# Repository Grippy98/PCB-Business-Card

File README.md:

# PCB-Business-Card
---

Business Cards are always something that I’ve found to be sort of a nuisance. On one hand, they’re something that very few people ever have on hand, and on the other, when you do get one, you’re very likely to misplace or throw it away. That being said, they are a good way of sharing your contact details, and while I have made my own nicely designed ones on paper, I couldn’t help but think that I could make something better. My goal here was to make something that not only could I be proud to give out to possible recruiters or people I’d want to contact in the future, but I wanted to make something they’d actually WANT to keep with them or in their wallet.

Therefore I set out to design what you see before you, my very own extremely functional PCB business card. I credit it for a good number of job interviews I've gotten this past summer. It's a constant work in progress, but I'm very pleased with how it's turned out. 

###### A huge shoutout to Loann Boudin for his NFC design and for documenting it on Instructables: https://www.instructables.com/id/PCB-Business-Card-With-NFC/

### As far as the card’s functionality goes: 

1. 1S Lithium Battery Charger 
2. NFC Enabled - Have it setup to link to my Website/Resume (also demonstrates power harvesting to LED)
3. Simple logic probe that will tell you if a signal is high/low, oscillating or floating (the last two perhaps are especially useful)
4. Basic flash light (because why not) 
5. Metric/imperial Ruler
6. AWG Gauge 
7. References for trace widths in Mils 
8. Reference for PCB Font Sizes 
9. Reference for some standard component footprints

---

### Ordering Your Own

The Boards you see were made by JLC PCB with an ENIG finnish, regular LEAD free also works. I do very much recommend you don't hand out leaded PCBs for people to handle and keep in their wallets, but that's just my two cents.

I have experimented with 0.6mm Thick Boards and above, but I recommend 0.8mm as it's thin enough while also being a bit more rigid. 

### BOM:
(TODO - fill out when I have some more time, consult schematic otherwise)
1x BRCL4054BME Power Management IC

### Notes on Soldering:

It's all rather easy to solder by hand, save for the QFN8 Package of the NFC IC, which is tough to get right, especially with Lead-free solder paste. I was able to make over 30 of these boards without defect and minor fixes by using solder masks and plenty of flux, but this is very much not beginner friendly.

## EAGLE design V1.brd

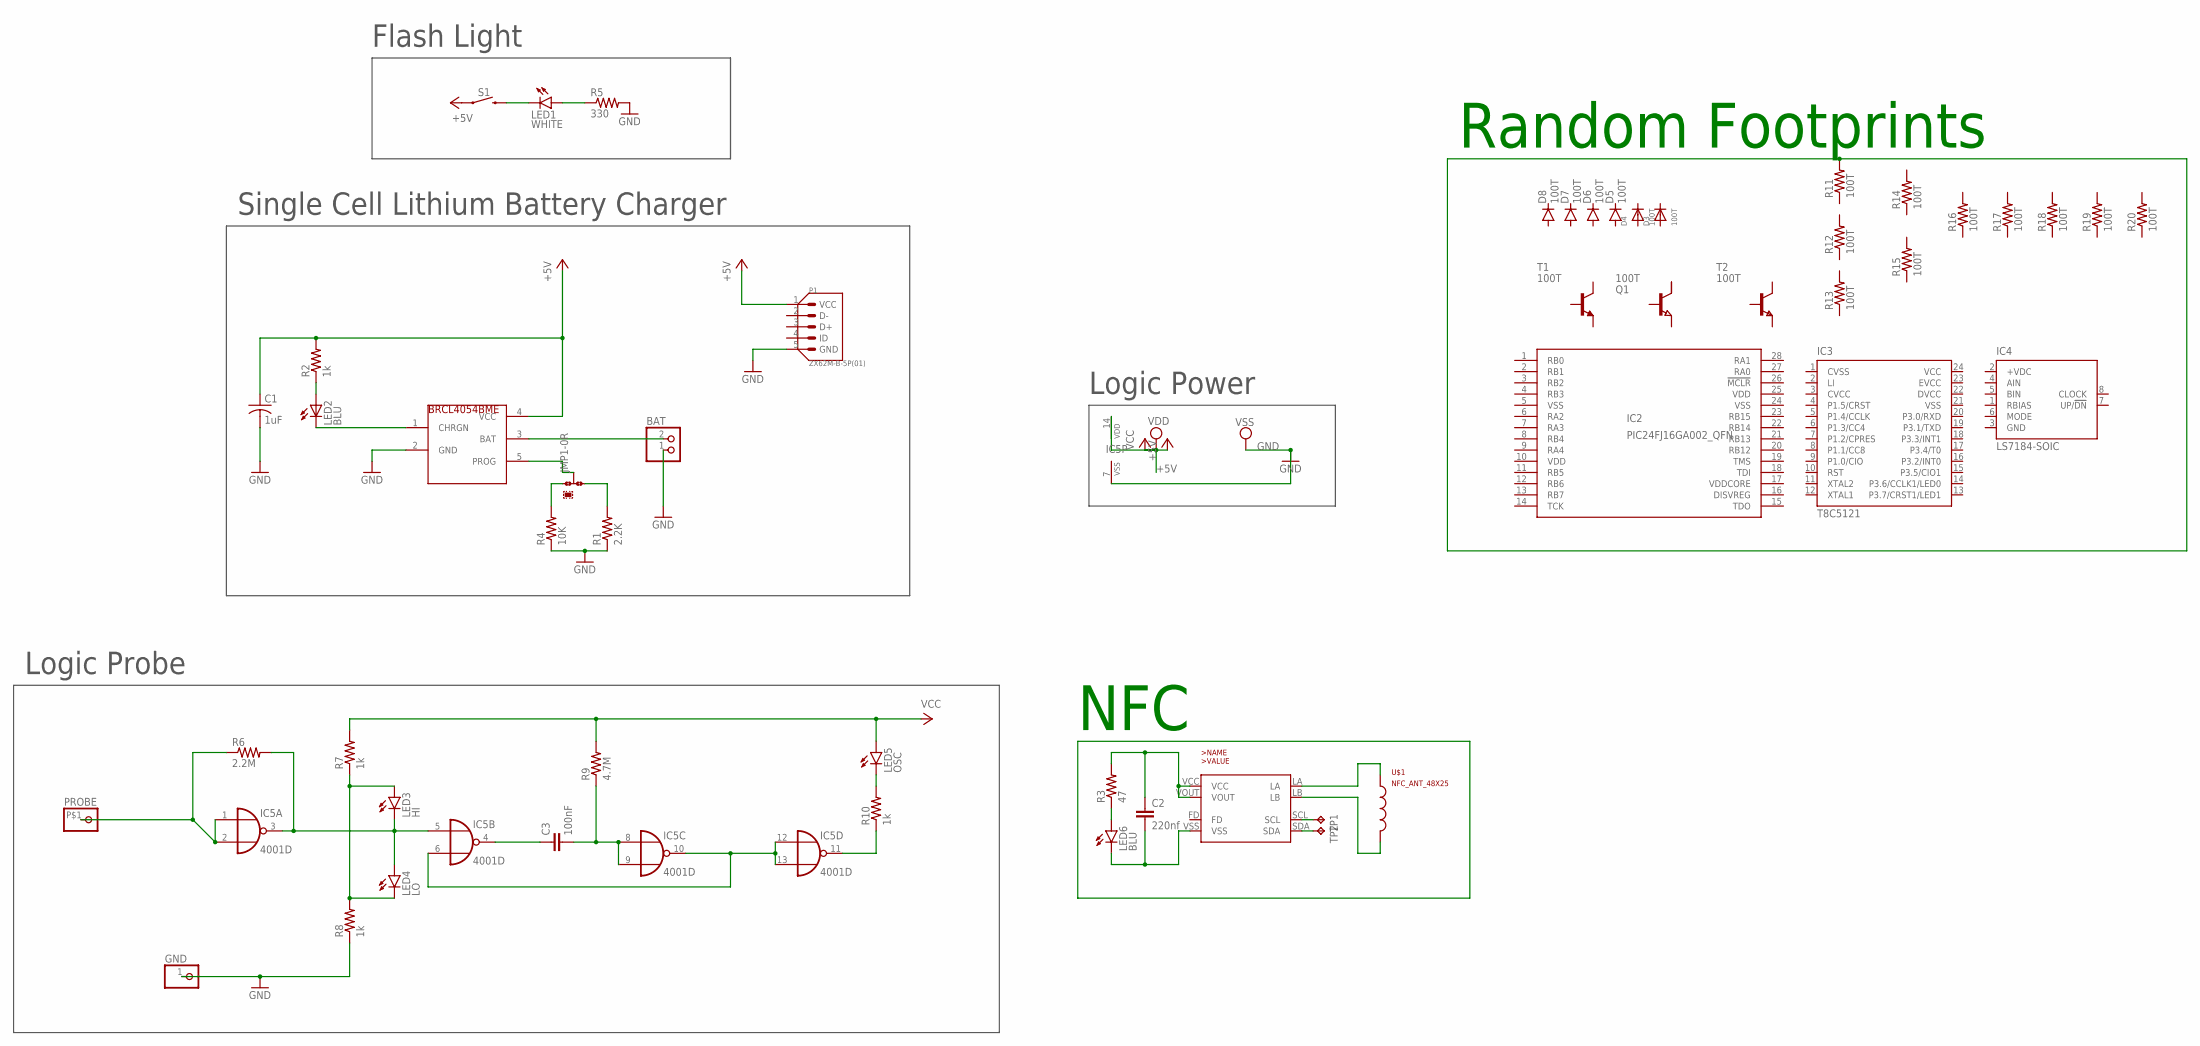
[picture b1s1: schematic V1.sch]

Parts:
BAT: JST_2PIN-SMT; JST-PH-2-SMT
C1: 1uF; C0402
C2: 220nf; C0402
C3: 100nF; C0402
D3: 100T; SMADIODE
D4: 100T; SOD-123
D5: 100T; SOD80C
D6: 100T; SOD323-R
D7: 100T; MICROMELF-R
D8: 100T; SC79_INFINEON
GND: PINHD-1X1; 1X01
IC2: PIC24FJ16GA002_QFN; QFN28-ML_6X6MM
IC3: T8C5121; SSOP24
IC4: LS7184-SOIC; SOIC08
IC5: 4001D; SO14
JMP1: 0R-JUMPA; A0R-JMP
LED1: WHITE; LED3MM
LED2: BLU; CHIP-LED0603
LED3: HI; SML0603
LED4: LO; SML0603
LED5: OSC; SML0603
LED6: BLU; SML0603
NT3H1101: NT3H1101; XQFN8
P1: ZX62M-B-5P(01); HRS_ZX62M-B-5P(01)
PROBE: PINHD-1X1-BIGPOGO; 1X1-BIGPOGO
Q1: 100T; SOT89
R1: 2.2K; R0402
R2, R7, R8, R10: 1k; R0402
R3: 47; R0402
R4: 10K; R0402
R5: 330; R0402
R6: 2.2M; R0402
R9: 4.7M; R0402
R11, R12, R13: 100T; R0201
R14, R15: 100T; R0402
R16: 100T; R0603
R17: 100T; R0805
R18: 100T; R1206
R19: 100T; R1210
R20: 100T; R2010
S1: MOMENTARY-SWITCH-SPST-SMD-5.2-REDUNDANT; TACTILE_SWITCH_SMD_5.2MM
T1: 100T; SOT23-EBC
T2: 100T; SOT223
TP1, TP2: TPTP06R; TP06R
U$1: NFC_ANT_48X25
U$3: HX4054A; SOT23-5L

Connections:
+5V: C1.1, IC2.10 (VDD), IC2.25 (VDD), IC3.24 (VCC), IC5.14 (VDD), P1.1 (VCC), R2.2, S1.1, S1.2 (1), U$3.4 (VCC)
CVCC: IC3.3 (CVCC)
CVSS: IC3.1 (CVSS)
DVCC: IC3.22 (DVCC)
GND: BAT.1 (2), C1.2, GND.1, IC2.5 (VSS), IC2.24 (VSS), IC3.21 (VSS), IC4.3 (GND), IC5.7 (VSS), P1.5 (GND), R1.1, R4.1, R5.2, R8.1, U$3.2 (GND)
LI: IC3.2 (LI)
unnamed: JMP1.3, R1.2
unnamed: LED2.A, R2.1
unnamed: LED2.C, U$3.1 (CHRGN)
unnamed: BAT.2 (1), U$3.3 (BAT)
unnamed: JMP1.2, U$3.5 (PROG)
unnamed: LED1.A, R5.1
unnamed: IC5.6 (I1), IC5.10 (O), IC5.12 (I0), IC5.13 (I1)
unnamed: IC5.1 (I0), IC5.2 (I1), PROBE.P$1, R6.1
unnamed: LED3.A, LED4.C, R7.1, R8.2
unnamed: C3.2, IC5.8 (I0), R9.1
unnamed: NT3H1101.LA, U$1.A
unnamed: NT3H1101.LB, U$1.B, U$1.P$3 (B)
unnamed: C2.1, NT3H1101.VCC, NT3H1101.VOUT, R3.2
unnamed: LED6.A, R3.1
unnamed: C2.2, LED6.C, NT3H1101.VSS
unnamed: IC5.3 (O), IC5.5 (I0), LED3.C, LED4.A, R6.2
unnamed: NT3H1101.SDA, TP2.TP
unnamed: NT3H1101.SCL, TP1.TP
unnamed: C3.1, IC5.4 (O)
unnamed: IC5.11 (O), R10.1
unnamed: LED5.C, R10.2
unnamed: JMP1.1, R4.2
unnamed: LED1.K (C), S1.3 (2), S1.4 (2)
VCC: LED5.A, R7.2, R9.2
VDDCORE: IC2.17 (VDDCORE)

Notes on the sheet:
Logic Probe
Single Cell Lithium Battery Charger
Flash Light
Logic Power
Random Footprints
NFC

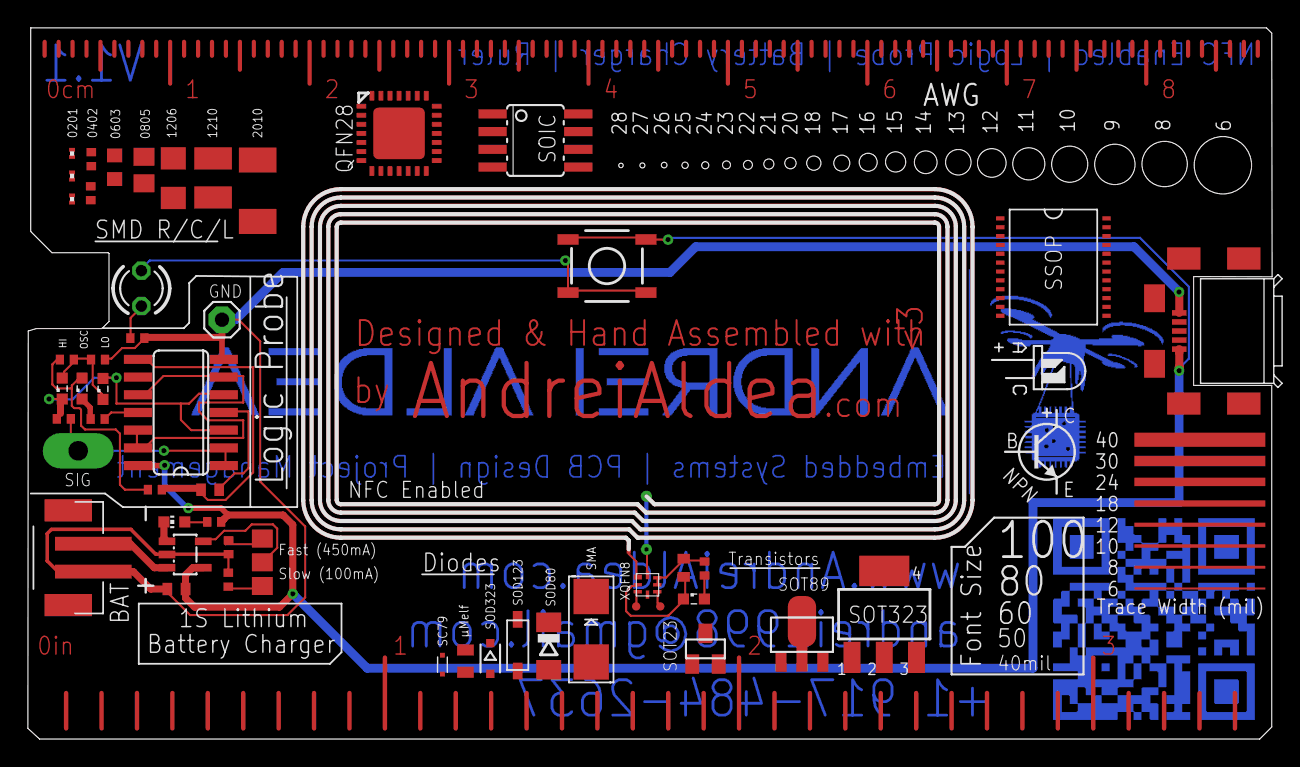
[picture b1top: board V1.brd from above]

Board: 2 copper layers, 89.2 x 51.0 mm, 57 parts (1 on the bottom side), 26 nets.

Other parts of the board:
E$54: NPN-SYMB
E$74: LED-GUIDE
U$2: IMPERIAL
U$4: METRIC

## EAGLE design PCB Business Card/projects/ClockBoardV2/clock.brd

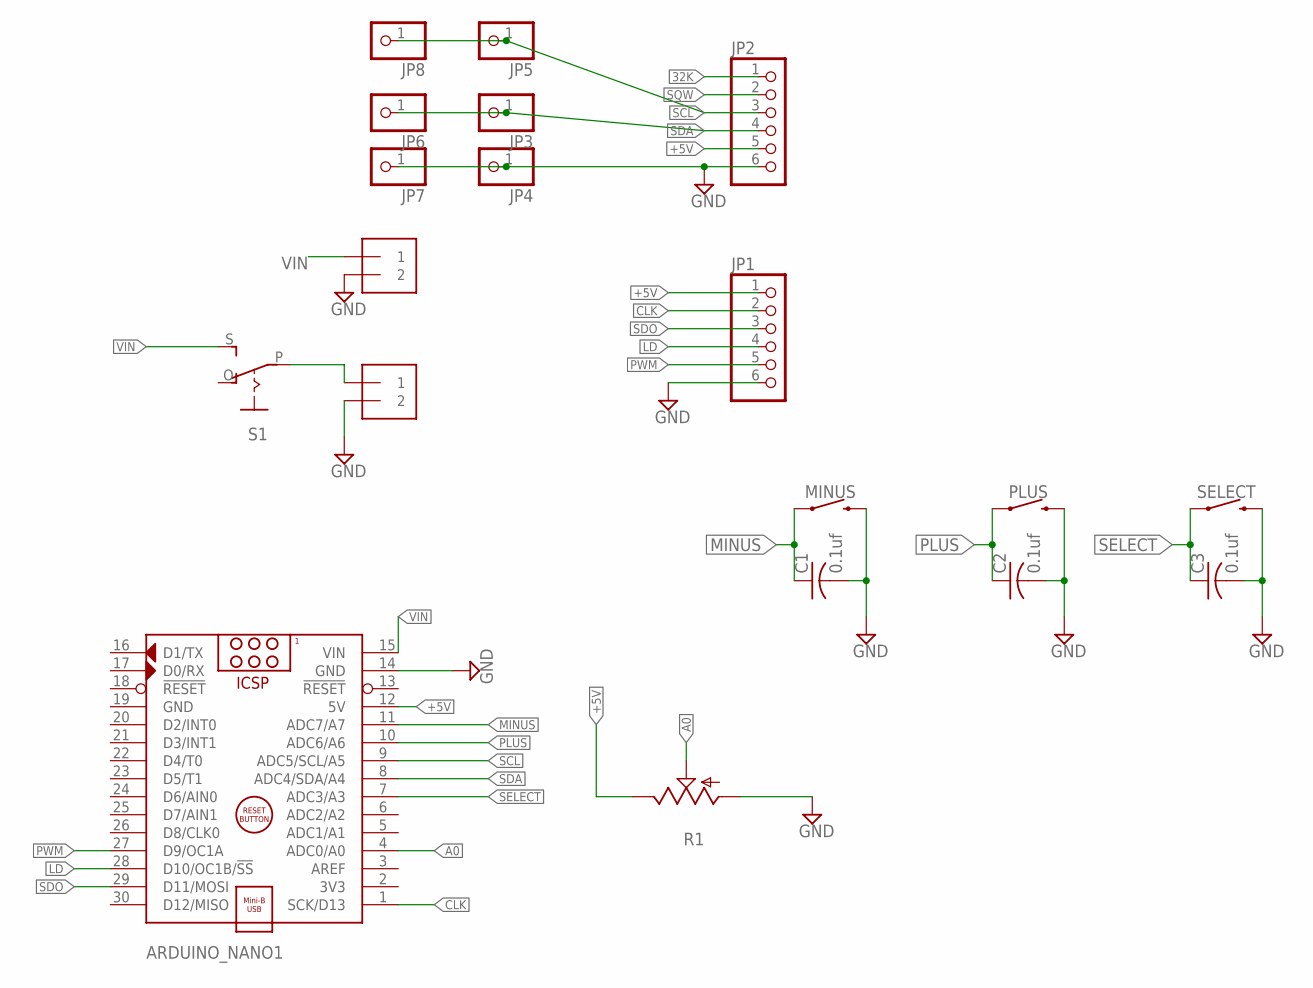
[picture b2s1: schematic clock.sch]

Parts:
ARDUINO_NANO1: ARDUINO_NANO
C1, C2, C3: 0.1uf; C025-025X050
J1, J2: 1X2-3.5MM
JP1, JP2: PINHD-1X6; 1X06
JP3, JP4, JP5, JP6, JP7, JP8: PINHD-1X1; 1X01
MINUS: MOMENTARY-SWITCH-SPST-PTH-6.0MM; TACTILE_SWITCH_PTH_6.0MM
PLUS: MOMENTARY-SWITCH-SPST-PTH-6.0MM; TACTILE_SWITCH_PTH_6.0MM
R1: TRIM_US-RS3; RS3
S1: EG1218S; EG1218
SELECT: MOMENTARY-SWITCH-SPST-PTH-6.0MM; TACTILE_SWITCH_PTH_6.0MM

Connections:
32K: JP2.1
+5V: ARDUINO_NANO1.12 (5V), JP1.1, JP2.5, R1.E
A0: ARDUINO_NANO1.4 (ADC0/A0), R1.S
CLK: ARDUINO_NANO1.1 (SCK/D13), JP1.2
GND: ARDUINO_NANO1.14 (GND), ARDUINO_NANO1.19 (GND), C1.2, C2.2, C3.2, J1.2, J2.2, JP1.6, JP2.6, JP4.1, JP7.1, MINUS.3 (2), PLUS.3 (2), R1.A, SELECT.3 (2)
LD: ARDUINO_NANO1.28 (D10/OC1B/!SS), JP1.4
MINUS: ARDUINO_NANO1.11 (ADC7/A7), C1.1, MINUS.1
unnamed: J1.1, S1.P
PLUS: ARDUINO_NANO1.10 (ADC6/A6), C2.1, PLUS.1
PWM: ARDUINO_NANO1.27 (D9/OC1A), JP1.5
SCL: ARDUINO_NANO1.9 (ADC5/SCL/A5), JP2.3, JP5.1, JP8.1
SDA: ARDUINO_NANO1.8 (ADC4/SDA/A4), JP2.4, JP3.1, JP6.1
SDO: ARDUINO_NANO1.29 (D11/MOSI), JP1.3
SELECT: ARDUINO_NANO1.7 (ADC3/A3), C3.1, SELECT.1
SQW: JP2.2
VIN: ARDUINO_NANO1.15 (VIN), J2.1, S1.S

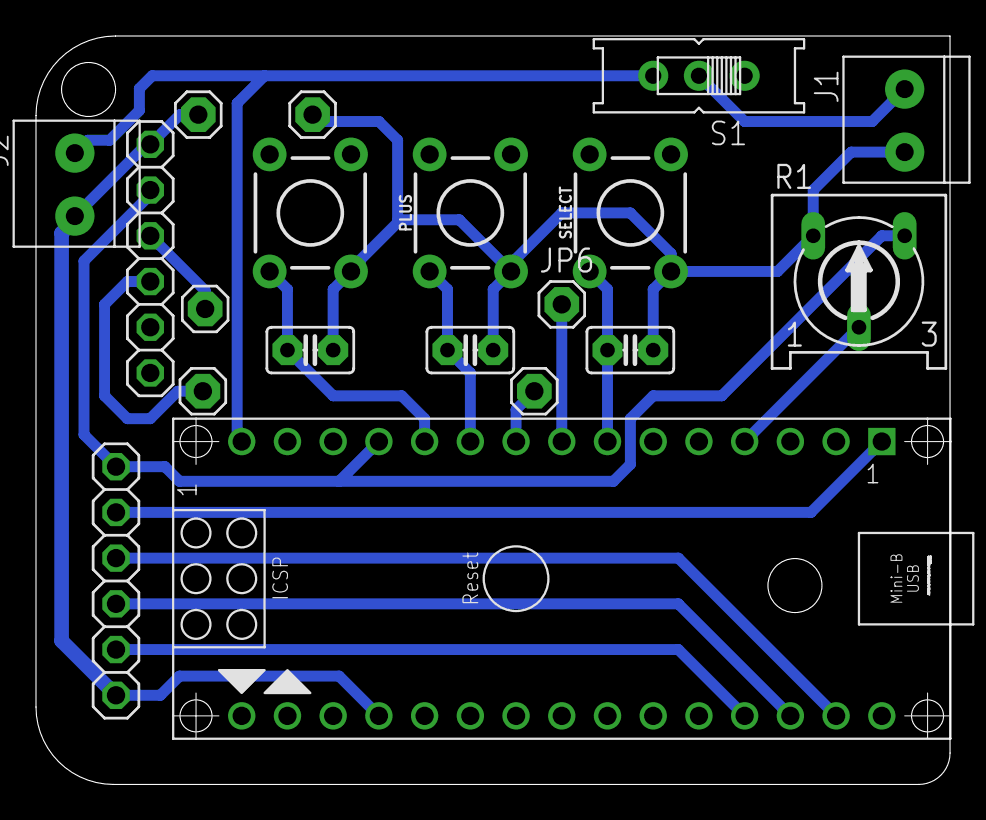
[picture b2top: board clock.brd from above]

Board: 2 copper layers, 50.8 x 41.6 mm, 19 parts (0 on the bottom side), 14 nets.

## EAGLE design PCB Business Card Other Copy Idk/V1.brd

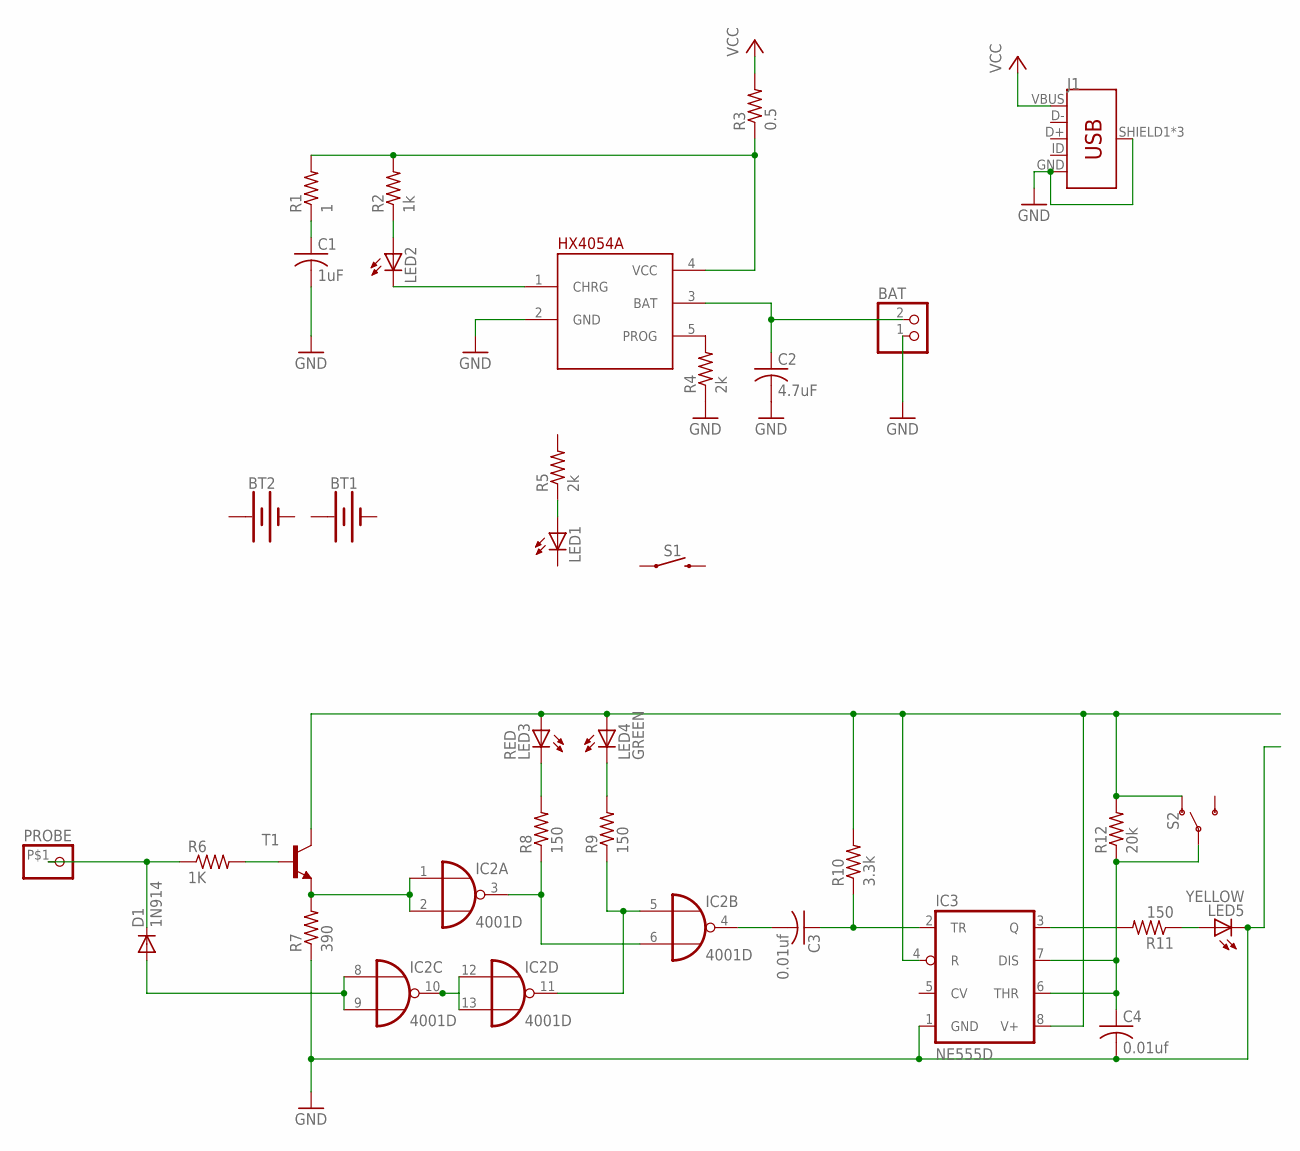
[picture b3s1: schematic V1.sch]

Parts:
BAT: JST_2PIN-SMT; JST-PH-2-SMT
BT1, BT2: BATTERY-12MM_SMD; BATTCON_12MM
C1: 1uF; C0402
C2: 4.7uF; C0402
C3, C4: 0.01uf; C0402
D1: 1N914; SOD323-W
IC2: 4001D; SO14
IC3: NE555D; SO08
J1: USB_MICRO-BREDUCED_PASTE; USB-B-MICRO-SMD_RED_PASTE
LED1: LED3MM
LED2: LEDCHIP-LED0603; CHIP-LED0603
LED3: RED; CHIP-LED0603
LED4: GREEN; CHIP-LED0603
LED5: YELLOW; CHIP-LED0603
PROBE: PINHD-1X1-BIGPOGO; 1X1-BIGPOGO
R1: 1; R0201
R2: 1k; R0201
R3: 0.5; R0402
R4: 2k; R0201
R5: 2k; R0603
R6: 1K; R0402
R7: 390; R0402
R8, R9, R11: 150; R0402
R10: 3.3k; R0402
R12: 20k; R0402
S1: MOMENTARY-SWITCH-SPST-SMD-5.2-REDUNDANT; TACTILE_SWITCH_SMD_5.2MM
S2: SWITCH-SPDT-PTH-11.6X4.0MM; SWITCH_SPDT_PTH_11.6X4.0MM
T1: MMBT2222ALT1-NPN-SOT23-BEC; SOT23-BEC
U$3: HX4054A; SOT23-5L

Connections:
+: BT1.PWR@1 (+), BT2.PWR@1 (+)
-: BT1.GND (-), BT2.GND (-)
GND: BAT.1 (2), C1.2, C2.2, C4.2, IC3.1 (GND), J1.GND, J1.SHIELD1 (SHIELD), J1.SHIELD2 (SHIELD), J1.SHIELD3 (SHIELD), LED5.C, R4.1, R7.1, U$3.2 (GND)
unnamed: C1.1, R1.1
unnamed: R1.2, R2.2, R3.1, U$3.4 (VCC)
unnamed: LED2.A, R2.1
unnamed: LED2.C, U$3.1 (CHRG)
unnamed: BAT.2 (1), C2.1, U$3.3 (BAT)
unnamed: R4.2, U$3.5 (PROG)
unnamed: LED1.A, R5.1
unnamed: R6.2, T1.B
unnamed: D1.C, PROBE.P$1, R6.1
unnamed: D1.A, IC2.8 (I0), IC2.9 (I1)
unnamed: IC2.10 (O), IC2.12 (I0), IC2.13 (I1)
unnamed: IC2.1 (I0), IC2.2 (I1), R7.2, T1.E
unnamed: LED3.C, R8.2
unnamed: LED4.C, R9.2
unnamed: IC2.3 (O), IC2.6 (I1), R8.1
unnamed: IC2.5 (I0), IC2.11 (O), R9.1
unnamed: LED5.A, R11.1
unnamed: IC3.3 (Q), R11.2
unnamed: C3.2, IC2.4 (O)
unnamed: C3.1, IC3.2 (TR), R10.1
unnamed: C4.1, IC3.6 (THR), IC3.7 (DIS), R12.1, S2.2
unnamed: IC3.4 (R), IC3.8 (V+), LED3.A, LED4.A, R10.2, R12.2, S2.1 (O), T1.C
VCC: J1.VBUS, R3.2
VDD: IC2.14 (VDD)
VSS: IC2.7 (VSS)

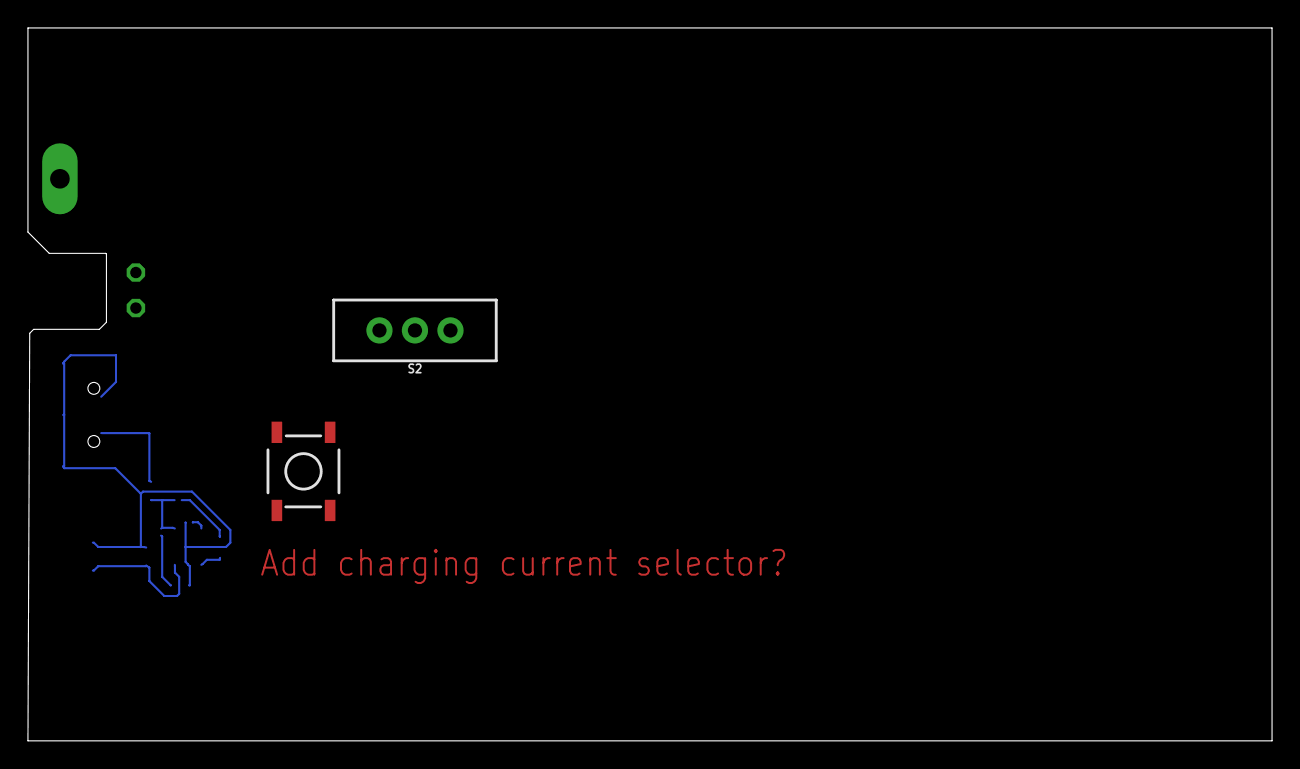
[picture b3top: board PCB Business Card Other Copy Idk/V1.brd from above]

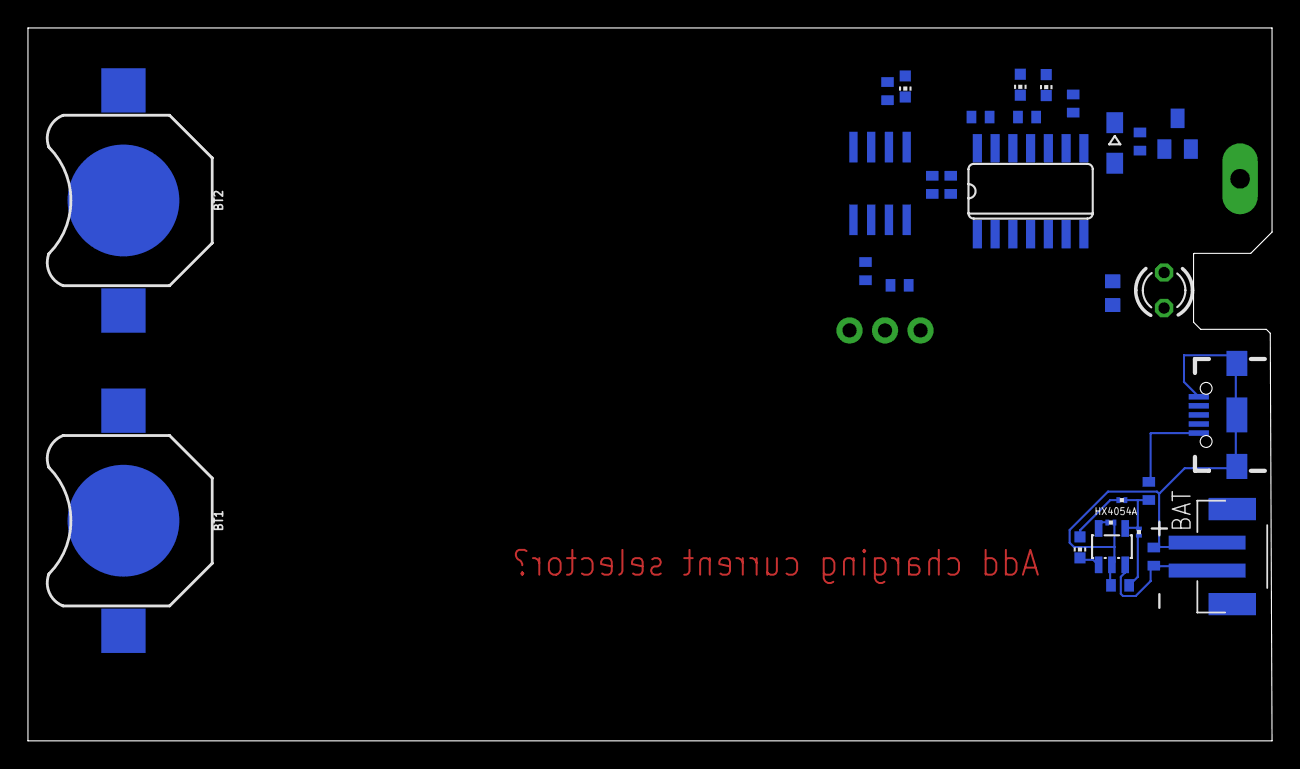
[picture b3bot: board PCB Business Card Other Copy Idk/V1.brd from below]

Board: 2 copper layers, 89.0 x 51.0 mm, 35 parts (30 on the bottom side), 26 nets.

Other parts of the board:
U$1: METRIC
U$2: IMPERIAL

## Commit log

2019-07-24 O no I'm getting ideas
2019-07-25 Really Proud of How its TUrning out... Almost done
2019-07-26 V1 Completed
2019-07-29 Version that went into production
2019-08-02 4001 and 74 Series logic Pinout is Different... DOH
2019-08-26 I made changes aparently
2019-08-29 V1.1 Ordered From JLC
2020-04-01 Cleanning Up
2020-04-01 Fixed Images
2020-04-01 Cleanup

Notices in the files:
parts and their libraries:
SparkFun-Switches: Licensing: Creative Commons ShareAlike 4.0 International - https://creativecommons.org/licenses/by-sa/4.0
